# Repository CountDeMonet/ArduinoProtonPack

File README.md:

# Arduino Based Ghostbusters Proton Pack
Arduino Code for a Ghostbusters Neutrino Wand and Proton Pack

I'm in the process of building a proton pack for my son and this is the progress I have made so far. I have included the models for 3d printing, all sounds but the ghostbusters theme song, and the arduino code to control all of this. The models for 3d printing are scaled to 83%. The proton pack models are also mirrored for a left handed users pack. Once I have some time I'll post non-mirrored files. 

The models are based off the following things on thingiverse: 
* Main base model for the pack: https://www.thingiverse.com/thing:2479141
* Base model for the proton wand: https://www.thingiverse.com/thing:1128019
* Full scale proton wand the 83% one is based on: https://www.thingiverse.com/thing:2334883
* And a clippard valve with text: https://www.thingiverse.com/thing:2286284

This pack utilizes many off the shelf products for the electronics to make the build as easy as possible. Total cost is around $80 for the parts if sourced from amazon. You can find cheaper on ebay

* 1 arduino nano. You get 3 for $11.86: https://www.amazon.com/gp/product/B0713XK923
* 2 power converters to adjust the 11.1v lipo to 5v. You get 6 for $9.69: https://www.amazon.com/gp/product/B01MQGMOKI
* 1 Adafruit Audio FX Sound Board. It's the most expensive part at $23.80 but is awesome to work with: https://www.amazon.com/gp/product/B00Q3U42DM
* Audio amp $6.01 each: https://www.amazon.com/gp/product/B00PY2YSI4
* small speaker for my 83% scale build. You get 2 for $8.05. https://www.amazon.com/gp/product/B00NQ0LHNA
* 4 neopixel jewels for the cyclotron @ 5.49 each: https://www.amazon.com/gp/product/B0105VMT4S
* 1 neopixel jewels for the end of the wand @ 5.49 each: https://www.amazon.com/gp/product/B0105VMT4S
* two 8 neopixel light stick for the powercell @9.99 each: https://www.amazon.com/Adafruit-NeoPixel-Arduino-Integrated-Drivers/dp/B00IEDH26K
* Individual neopixels for venting, wand lights, and for the cyclotron if doing the spirit version. 100 for $16: https://www.amazon.com/Kuman-WS2812B-Addressable-Arduino-littlergb/dp/B01M5BEO1C
* 4 toggle switches:https://www.amazon.com/gp/product/B00HGAKDIQ
* 1 button:  https://www.amazon.com/gp/product/B01IU898QA
* 11.1v lipo to power the whole thing: https://www.amazon.com/Gens-ace-Battery-2200mAh-Airplane/dp/B00WJN4LG0

I bought the light covers from digikey

https://www.digikey.com/product-detail/en/visual-communications-company-vcc/CLF_280_ATP/CLF_280_ATP-ND/4515437 - light near the clippard
https://www.digikey.com/product-detail/en/visual-communications-company-vcc/SMB_200_RTP/SMB_200_RTP-ND/4515614 - sloblo
https://www.digikey.com/product-detail/en/visual-communications-company-vcc/SML_190_CTP/SML_190_CTP-ND/4515623 - Vent light front
https://www.digikey.com/product-detail/en/visual-communications-company-vcc/CMC_321_YTP/CMC_321_YTP-ND/4515456 - Vent light rear (no led tied to this one)

For the optional bargraph we are using the SparkFun SX1509 expander board and some resitor networks/bargraphs from digikey. If you want to use the bargraph you need to move the code from the test file into the main file and overwrite the stub functions. Since I won't be using it in my son's pack I removed it from the main file 
https://learn.sparkfun.com/tutorials/sx1509-io-expander-breakout-hookup-guide

* https://www.digikey.com/product-detail/en/sparkfun-electronics/BOB-13601/1568-1186-ND/5673772
* https://www.digikey.com/product-detail/en/bourns-inc/4611X-101-331LF/4611X-101-331LF-ND/3787988
* https://www.digikey.com/product-detail/en/bourns-inc/4606X-101-331LF/4606X-1-331LF-ND/1088983
* https://www.digikey.com/product-detail/en/sunled/XGUYX10D/1497-1086-5-ND/4745985
* https://www.digikey.com/product-detail/en/sunled/XGUYX5D/1497-1087-5-ND/4745584

Here's a video of the whole shebang put together

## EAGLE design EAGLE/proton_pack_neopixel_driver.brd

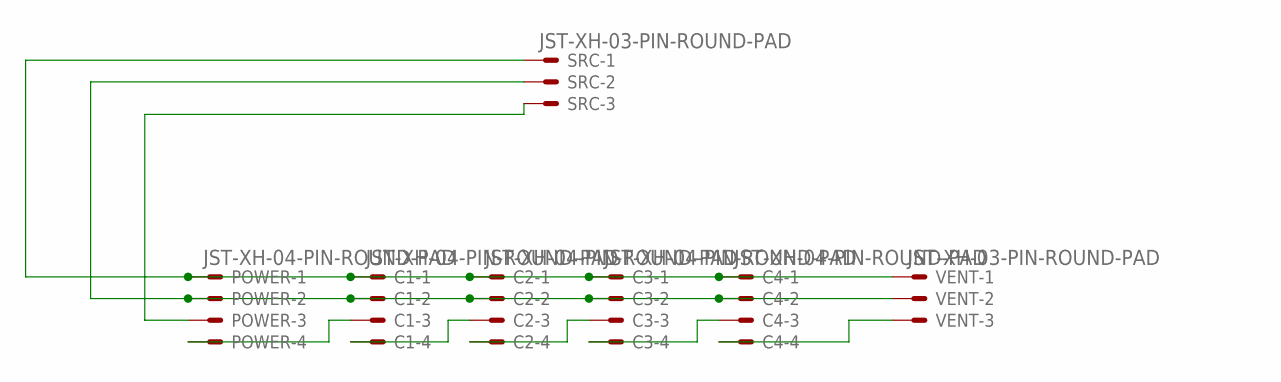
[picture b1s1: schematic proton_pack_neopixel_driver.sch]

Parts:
C1, C2, C3, C4: JST-XH-04-PIN-ROUND-PAD; JST-XH-04-PACKAGE-ROUND-PAD
POWER: JST-XH-04-PIN-ROUND-PAD; JST-XH-04-PACKAGE-ROUND-PAD
SRC: JST-XH-03-PIN-ROUND-PAD; JST-XH-03-PACKAGE-ROUND-PAD
VENT: JST-XH-03-PIN-ROUND-PAD; JST-XH-03-PACKAGE-ROUND-PAD

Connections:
unnamed: C1.3, POWER.4
unnamed: C1.4, C2.3
unnamed: C2.4, C3.3
unnamed: C3.4, C4.3
unnamed: C4.4, VENT.3
unnamed: C1.2, C2.2, C3.2, C4.2, POWER.2, SRC.2, VENT.2
unnamed: C1.1, C2.1, C3.1, C4.1, POWER.1, SRC.1, VENT.1
unnamed: POWER.3, SRC.3

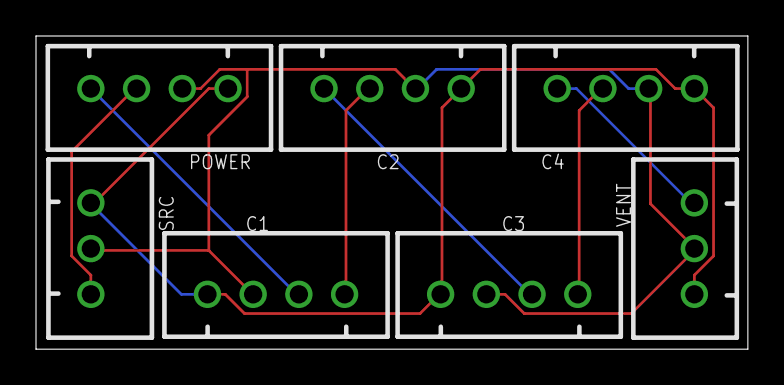
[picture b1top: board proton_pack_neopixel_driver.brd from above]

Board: 2 copper layers, 39.5 x 17.4 mm, 7 parts (0 on the bottom side), 8 nets.

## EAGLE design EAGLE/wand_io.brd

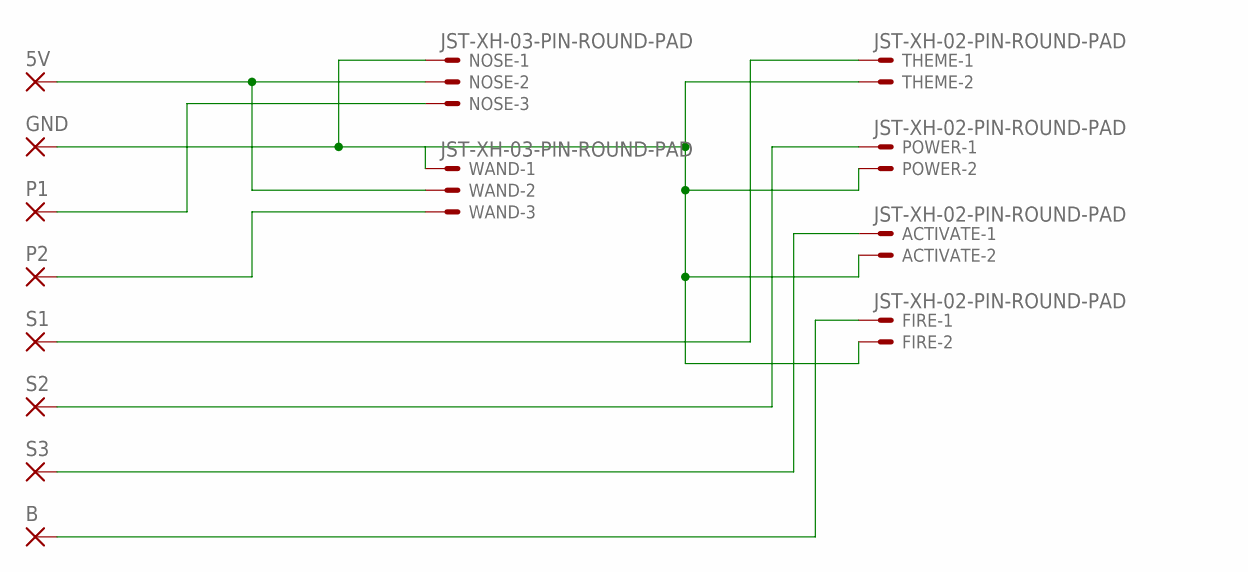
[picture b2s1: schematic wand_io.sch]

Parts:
5V: 2,54/1,1
ACTIVATE: JST-XH-02-PIN-ROUND-PAD; JST-XH-02-PACKAGE-ROUND-PAD
B: 2,54/1,1
FIRE: JST-XH-02-PIN-ROUND-PAD; JST-XH-02-PACKAGE-ROUND-PAD
GND: 2,54/1,1
NOSE: JST-XH-03-PIN-ROUND-PAD; JST-XH-03-PACKAGE-ROUND-PAD
P1, P2: 2,54/1,1
POWER: JST-XH-02-PIN-ROUND-PAD; JST-XH-02-PACKAGE-ROUND-PAD
S1, S2, S3: 2,54/1,1
THEME: JST-XH-02-PIN-ROUND-PAD; JST-XH-02-PACKAGE-ROUND-PAD
WAND: JST-XH-03-PIN-ROUND-PAD; JST-XH-03-PACKAGE-ROUND-PAD

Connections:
unnamed: ACTIVATE.2, FIRE.2, GND.1, NOSE.1, POWER.2, THEME.2, WAND.1
unnamed: 5V.1, NOSE.2, WAND.2
unnamed: B.1, FIRE.1
unnamed: NOSE.3, P1.1
unnamed: P2.1, WAND.3
unnamed: S1.1, THEME.1
unnamed: POWER.1, S2.1
unnamed: ACTIVATE.1, S3.1

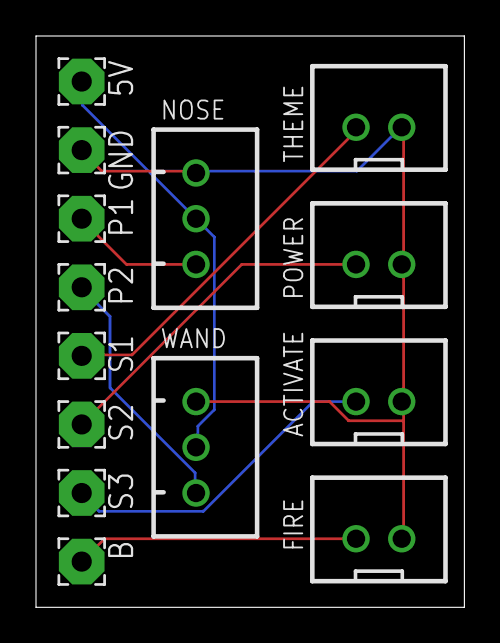
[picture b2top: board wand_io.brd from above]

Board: 2 copper layers, 23.8 x 31.7 mm, 14 parts (0 on the bottom side), 8 nets.

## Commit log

2017-09-11 Add the model for the proton wand and most of the sounds
2017-09-11 add the libraries used
2017-09-11 add main wand code and the optional bargraph code
2017-09-11 add the models for the proton pack for printing. Currently exported for a left handed pack
2017-09-11 add link to video
2017-09-15 new ion arm that prints easier and easier to finish, more accurate syncgen part, and an m4 motherboard mount
2017-09-15 repaired model
2017-09-15 loom mount for the syncgen connection
2017-09-15 added a bottom to the ion mount. This will give more surface area for the glue
2017-09-18 moved some pins around for simplicity, new startup/shutdown animations, initial crack at cyclotron animation
    see https://www.youtube.com/watch?v=2o-0Lq8c1x0 for demo of current
    code. This is initial still and has not been optimized
2017-09-19 longer 30 second idle sound. While the 2 second was ok the pop every 2 seconds was not. This spaces it out nicer
2017-09-19 slowed down the nose strobe effect so more colors can be seen
2017-09-19 speed up the mid and warning intervals for the cyclotron
2017-09-23 added a new properly scaled HGA, an Nfilter with holes open for vent light, and a motherboard standoff for mounting to alice frame or pvc
2017-09-24 Added an option to use the ghostbusters game effect for the cyclotron
    For people that own a Spirit Proton Pack I have uploaded a very simple
    version of the code that simply does the powercell and cyclotron lights.
2017-09-24 add instructions for merging the bargraph code into the main neutrino_wand file
2017-09-25 some code cleanup
2017-09-25 First crack at the wand lights. Adds blinking top, orange black, red slowblo, and blue body when activated
2017-09-25 changed the top indicator to a warning indicator. Cleanup
2017-09-26 Added the missing models for the front handle and nose section
2017-09-26 include a mount for individual neopixel led's.
    place pixel in mount, glue mount where you want it, and hot glue the led
    in so it can be removed if needed.
2017-09-27 Add 2 neopixels to the powercell/cyclotron chain that can be used to show a venting light in the nfilter
2017-09-27 Body light only one when active and not venting, increase speed of mid speed firing animation. remove unused animation
2017-09-27 More work on the wand lights, new cyclotron animation option for startup
    SloBlo now blinks when booting/venting, rear light and vent light are
    tied to activate switch, top light flashes yellow after firing 5 seconds
    and fast red after firing for 10 seconds. As pack vents all wand lights
    shut down, sloblo then flashes red. 2 more neopixels added to the
    powercell/cyclotron chain for doing the nfilter venting effect
2017-09-27 made the dialog tracks optional.
2017-09-27 Fixed the powercell configuration and added the abiltiy to offset the start led in the sequence.
    My powercell can only fit 14 led's in the window so I had to add the
    offset and fix the total so I can use only the middle 14 led's
2017-09-28 individual neopixel holder and powerstrip mount for the powercell
2017-09-29 Some code cleanup, add 2 neopixels to venting light, remove dialog randomizer
    Dialog randomizer was destabalizing the code. I'm not sure why but for
    now I'm removing that bit. Will find another way to do it. TBH it wasn't
    that random anyway.
2017-09-29 fixed dialog indexes
2017-09-30 add 4 individual neopixel mount for the nfilter
2017-09-30 quick fritzing diagram of how things are connected minus the bar graph
2017-09-30 Updated circuit diagrams. Added one for a the spirit halloween upgrade
2017-09-30 Adding diagram full code with bargraph
2017-10-01 fixed an issue with the diagram. Added an option that
2017-10-01 new battery icon. All lipos in this setup are 11.1v
2017-10-07 Update diagram, printing the tube connectors now. Also new ion rods and ribbon cable mount
2017-10-07 more model updates
2017-10-08 remodelled the back panel knob with less detail. For such a small item my printer can't print it well with the detail so simplified
2017-10-11 Helper boards for simpler connections. Wand switch and button inputs and neopixel light connections
2017-10-11 update the light board to use the same jst lib as the other one.
2017-10-11 move the audio board pins up one for easier soldering, remove a second digital read of the act as it's not needed, update brightness
2017-10-11 removed example diagram for future features
2017-10-14 now that I've built the minimal spirit circuit here is the updated code and diagram. 5v out on the buck converter
2017-10-14 a few models for helping to mount the cyclotron and powercell lights
2017-10-14 updated diagram for one neopixel per cyclotron hole
2017-10-15 model for powercell updated. I had it reversed
2017-10-15 Alternate Spirit Circuit without the buck converter for simpler wiring
2017-10-16 Mount for the gun and a gun track for it.
2017-10-16 made the gun track 125mm instead of 120 to better fit the gun
2017-10-17 some model updates
2017-10-19 add in missing connector for the trigger box
2017-10-19 use white light for wand vent light, in normal fire just stop the track. The tail happens if firing a lot.
2017-10-20 The 5 neopixel stick for $8 deal is gone from amazon so linking to the adafruit component that is needed
2017-10-20 updated track names and added a new click and stream shutdown sound for short bursts. I like this better
2017-10-23 undid the mirroring of the pack. Now it's in the standard orientation.
2017-11-19 Add boot animations for spirit pack when power is applied. Option short sound for idle
2017-11-19 Fixes
2017-12-13 Reduce memory usage ( found by Grogking)
2018-01-10 adding in the full source with bargraph.
2018-03-01 updated the timer variables to all be unsigned long. Fixes an animation hiccup that could occur
2018-03-01 updated some of the timer variables. Should resolve some random animation issues
2018-03-05 update the timing code to force unsinged long for all comparisons
2018-03-06 updated sound board pinout to match the diagram
2018-03-10 Thanks to Andreas Werding for updating the diagram for the pack with bargraph.
2018-08-06 add the back brace standoff
2018-08-09 more models for the back brace
2018-08-14 some more wiring diagram help for using the eagle boards
2018-09-13 trying to sync up the cyclotron and powercell animations so one full powercell for each cyclotron light
2018-09-17 found the schematics for the boards.
2018-09-17 Fritzing Files
2018-10-10 Remove code stop if the audio board is not working.
2018-10-10 Remove stop if audio board is not working.
2018-10-10 update comments
2018-10-10 clarify comments
2019-09-18 simplfy the relay code
2021-12-17 pics of the bar graph proto board
